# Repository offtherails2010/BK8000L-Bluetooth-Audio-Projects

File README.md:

# BK8000L-Bluetooth-Audio-Projects
A Few Different Project that will utilise the BK8000L Bluetooth Audio Component-PCB, including a 'wireless' Bluetooth heatset with very high quality Microphone and Converting a Small 20 Watt Computer 2.1 Sound Box (Subwoofer and 2 Satelite Speakers for treble) into a Bluetooth Wireless Stand-alone Unit without needing wires to connect to the Computer of any other Bluetooth Audio Device :)

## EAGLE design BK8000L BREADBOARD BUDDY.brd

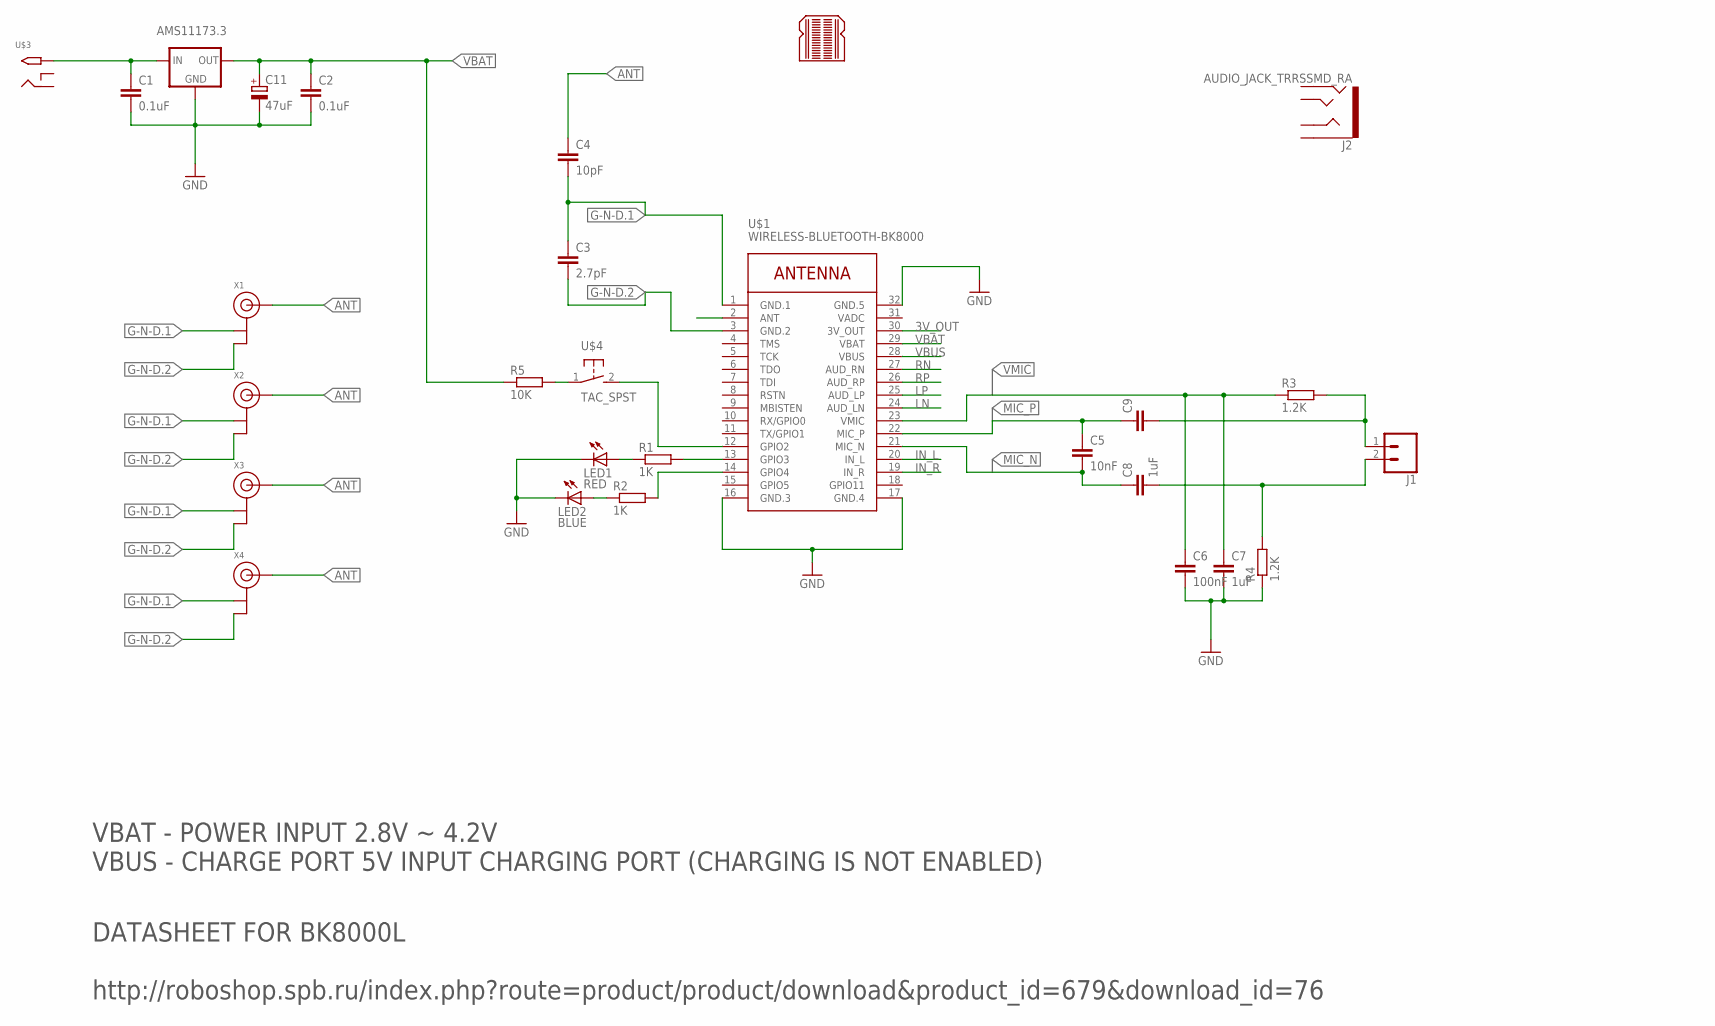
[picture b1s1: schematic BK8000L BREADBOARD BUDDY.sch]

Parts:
C1, C2: 0.1uF; C1206
C3: 2.7pF; C1206
C4: 10pF; C1206
C5: 10nF; C0603
C6: 100nF; C0603
C7, C8: 1uF; C0603
C9: C-EUC0603; C0603
C11: 47uF; SMC_D
J1: CONN_02LOCK; 1X02_LOCK
J2: AUDIO_JACK_TRRSSMD_RA; AUDIO_JACK_3.5MM_TRRS_SMD_RA
LED1: RED; CHIPLED_1206
LED2: BLUE; CHIPLED_1206
LOGO1: BREADBOARD_PATTERN; BREADBOARD_SPACING
R1, R2: 1K; R1206
R3, R4: 1.2K; R0603
R5: 10K; R0603
U$1: WIRELESS-BLUETOOTH-BK8000
U$2: AMS11173.3; SOT223
U$3: 2.1MMJACKMTS; PJ-102B
U$4: TAC_SPST; TACTILE-SPST
X1, X2, X3, X4: ANTENNA_U.FL; U.FL

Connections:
3V_OUT: U$1.30 (3V_OUT)
ANT: C4.1, U$1.2 (ANT), X1.3 (SIGNAL), X2.3 (SIGNAL), X3.3 (SIGNAL), X4.3 (SIGNAL)
G-N-D.1: C3.1, C4.2, U$1.1 (GND.1), X1.1 (GND), X2.1 (GND), X3.1 (GND), X4.1 (GND)
G-N-D.2: C3.2, U$1.3 (GND.2), X1.2 (GND), X2.2 (GND), X3.2 (GND), X4.2 (GND)
GND: C1.2, C2.2, C6.2, C7.2, C11.-, LED1.C, LED2.C, R4.1, U$1.16 (GND.3), U$1.17 (GND.4), U$1.32 (GND.5), U$2.1 (GND)
IN_L: U$1.20 (IN_L)
IN_R: U$1.19 (IN_R)
LN: U$1.24 (AUD_LN)
LP: U$1.25 (AUD_LP)
MIC_N: C5.2, C8.1, U$1.21 (MIC_N)
MIC_P: C5.1, C9.1, U$1.22 (MIC_P)
unnamed: C1.1, U$2.3 (IN), U$3.TIP
unnamed: C9.2, J1.1, R3.2
unnamed: R5.2, U$4.1
unnamed: C8.2, J1.2, R4.2
unnamed: LED1.A, R1.1
unnamed: R1.2, U$1.13 (GPIO3)
unnamed: R2.2, U$1.14 (GPIO4)
unnamed: LED2.A, R2.1
unnamed: U$1.12 (GPIO2), U$4.2
RN: U$1.27 (AUD_RN)
RP: U$1.26 (AUD_RP)
VADC: U$1.31 (VADC)
VBAT: C2.1, C11.+, R5.1, U$1.29 (VBAT), U$2.2 (OUT), U$2.4 (OUT)
VBUS: U$1.28 (VBUS)
VMIC: C6.1, C7.1, R3.1, U$1.23 (VMIC)

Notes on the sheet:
DATASHEET FOR BK8000L http://roboshop.spb.ru/index.php?route=product/product/download&product_id=679&download_id=76
VBAT - POWER INPUT 2.8V ~ 4.2V VBUS - CHARGE PORT 5V INPUT CHARGING PORT (CHARGING IS NOT ENABLED)

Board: 2 copper layers, 28 parts (0 on the bottom side), 17 nets, no tracks yet.

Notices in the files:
parts and their libraries:
SparkFun-Aesthetics: Licensing: Creative Commons ShareAlike 4.0 International - https://creativecommons.org/licenses/by-sa/4.0
diy-modules: Released under the Creative Commons Attribution 4.0 International License: http://creativecommons.org/licenses/by/4.0
